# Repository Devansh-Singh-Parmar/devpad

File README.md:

# DevPad
This is my Macropad design, which I made from scratch. It has an open top to show the pcb design

# Specifications

<ul>
<li>16x Cherry MX Switches <br>
<li>1x XIAO RP2040 <br>
<li>16x Blank DSA Keycaps <br>
<li>4x M3x16 Bolt <br>
<li>1x EC11 Rotary Encoder</li>
</ul>

Others:
<ul>
<li>KMK Firmware
<li>macropad-case.stl
</ul>

<h3>Schematic-</h3>

<h3>Case</h3>

<h3>PCB</h3>

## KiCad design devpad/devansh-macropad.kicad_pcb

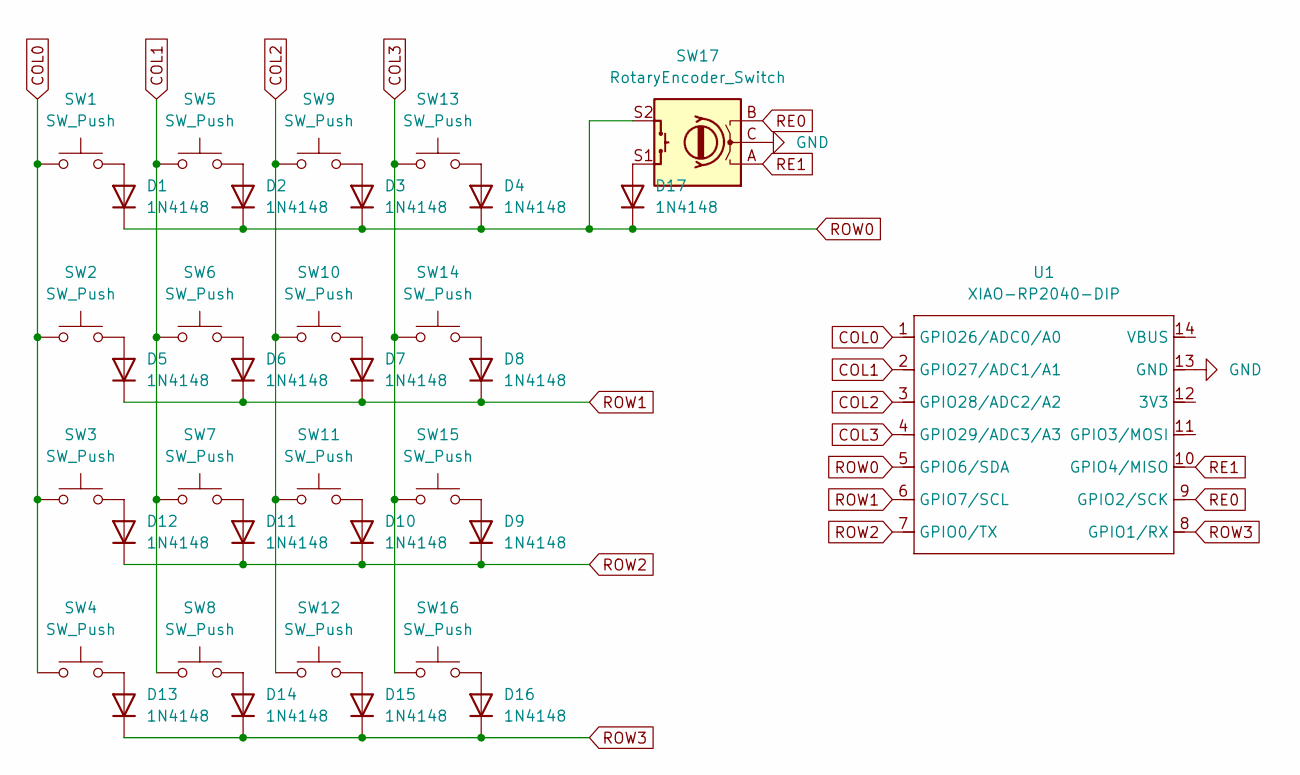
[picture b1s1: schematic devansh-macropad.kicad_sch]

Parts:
D1, D2, D3, D4, D5, D6, D7, D8, D9, D10, D11, D12, D13, D14, D15, D16, D17: 1N4148; D_DO-35_SOD27_P7.62mm_Horizontal
SW1, SW2, SW3, SW4, SW5, SW6, SW7, SW8, SW9, SW10, SW11, SW12, SW13, SW14, SW15, SW16: SW_Push; SW_Cherry_MX_1.00u_PCB
SW17: RotaryEncoder_Switch; RotaryEncoder_Alps_EC11E-Switch_Vertical_H20mm_CircularMoun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
U1: XIAO-RP2040-DIP

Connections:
COL0: SW1.1, SW2.1, SW3.1, SW4.1, U1.1 (GPIO26/ADC0/A0)
COL1: SW5.1, SW6.1, SW7.1, SW8.1, U1.2 (GPIO27/ADC1/A1)
COL2: SW9.1, SW10.1, SW11.1, SW12.1, U1.3 (GPIO28/ADC2/A2)
COL3: SW13.1, SW14.1, SW15.1, SW16.1, U1.4 (GPIO29/ADC3/A3)
GND: SW17.C, U1.13 (GND)
unnamed: D1.2 (A), SW1.2
unnamed: D2.2 (A), SW5.2
unnamed: D3.2 (A), SW9.2
unnamed: D4.2 (A), SW13.2
unnamed: D5.2 (A), SW2.2
unnamed: D6.2 (A), SW6.2
unnamed: D7.2 (A), SW10.2
unnamed: D8.2 (A), SW14.2
unnamed: D9.2 (A), SW15.2
unnamed: D10.2 (A), SW11.2
unnamed: D11.2 (A), SW7.2
unnamed: D12.2 (A), SW3.2
unnamed: D13.2 (A), SW4.2
unnamed: D14.2 (A), SW8.2
unnamed: D15.2 (A), SW12.2
unnamed: D16.2 (A), SW16.2
unnamed: D17.2 (A), SW17.S1
RE0: SW17.B, U1.9 (GPIO2/SCK)
RE1: SW17.A, U1.10 (GPIO4/MISO)
ROW0: D1.1 (K), D2.1 (K), D3.1 (K), D4.1 (K), D17.1 (K), SW17.S2, U1.5 (GPIO6/SDA)
ROW1: D5.1 (K), D6.1 (K), D7.1 (K), D8.1 (K), U1.6 (GPIO7/SCL)
ROW2: D9.1 (K), D10.1 (K), D11.1 (K), D12.1 (K), U1.7 (GPIO0/TX)
ROW3: D13.1 (K), D14.1 (K), D15.1 (K), D16.1 (K), U1.8 (GPIO1/RX)

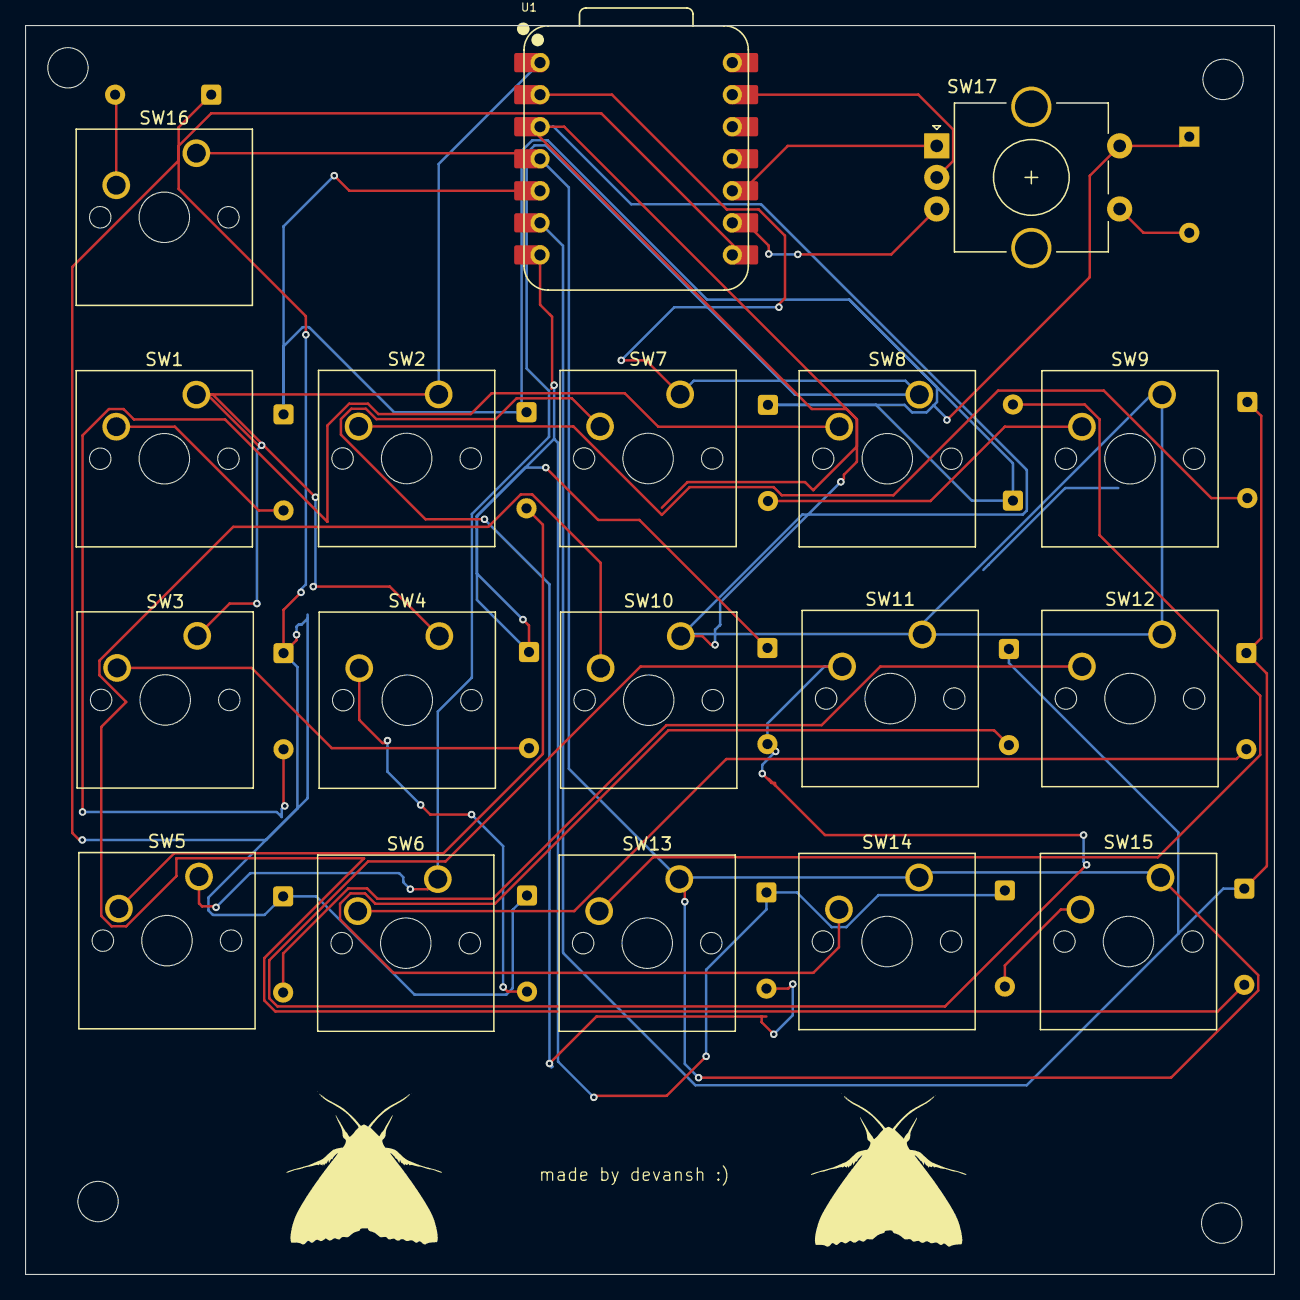
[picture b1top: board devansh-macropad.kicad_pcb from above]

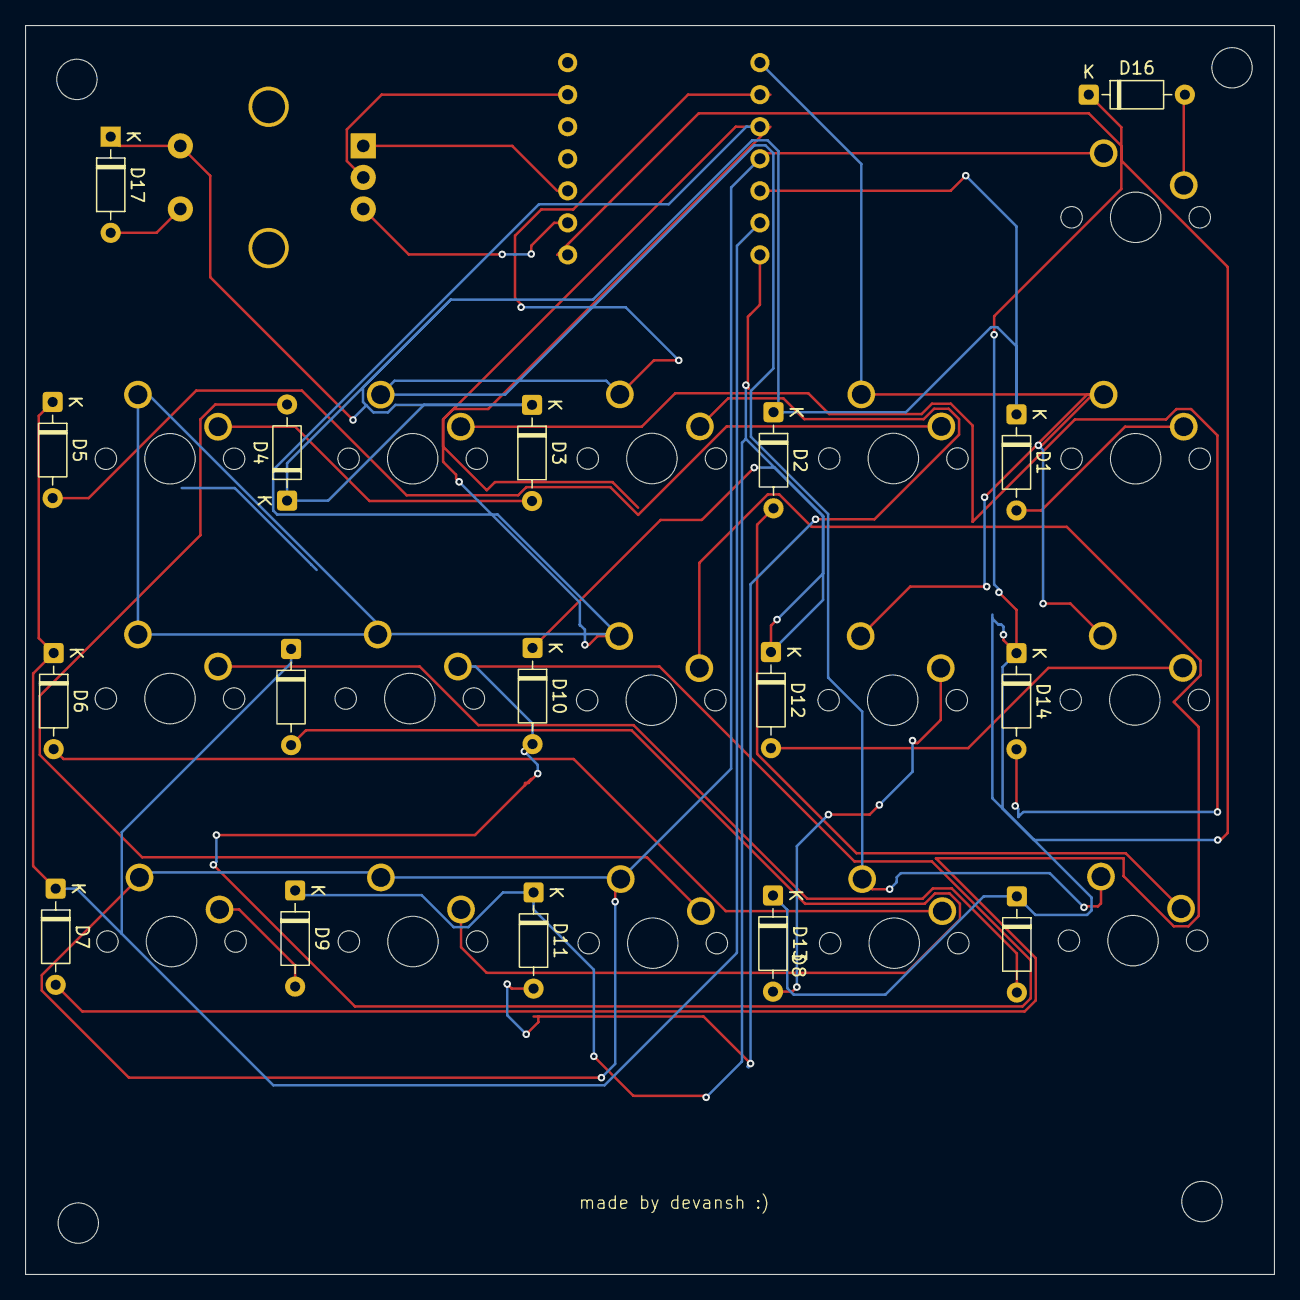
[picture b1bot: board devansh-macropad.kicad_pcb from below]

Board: 2 copper layers, 99.0 x 99.0 mm, 35 parts (17 on the bottom side), 28 nets.

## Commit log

2026-03-22 readme
2026-03-22 firmware
2026-03-22 step
2026-03-22 files
2026-03-22 cart
